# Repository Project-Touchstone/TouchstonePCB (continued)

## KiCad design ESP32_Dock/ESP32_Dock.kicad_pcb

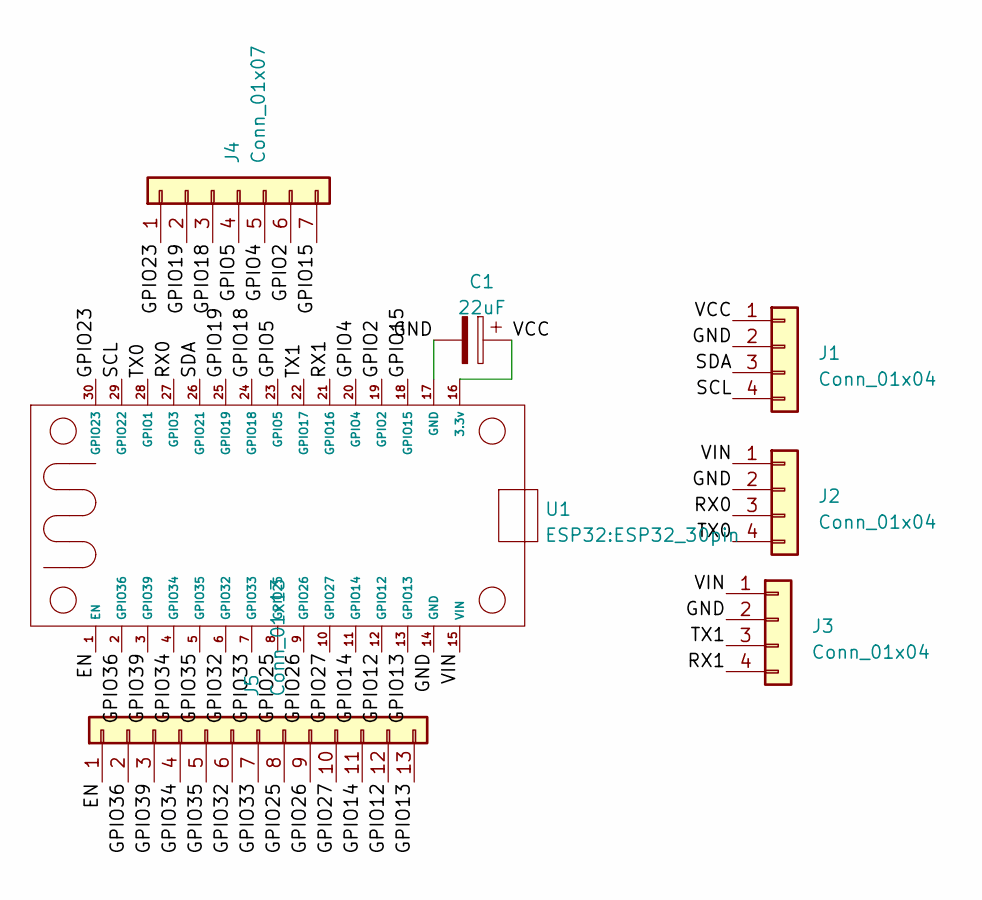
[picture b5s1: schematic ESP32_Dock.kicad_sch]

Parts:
C1: 22uF; C_Radial_D5.0mm_H11.0mm_P2.00mm
J1: Conn_01x04; PinHeader_1x04_P2.54mm_Vertical
J2: Conn_01x04; PinSocket_1x04_P2.54mm_Horizontal
J3: Conn_01x04; PinHeader_1x04_P2.54mm_Horizontal
J4: Conn_01x07; PinHeader_1x07_P2.54mm_Vertical
J5: Conn_01x13; PinHeader_1x13_P2.54mm_Vertical
U1: ESP32_30pin

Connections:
/EN: J5.1, U1.1 (EN)
/GND: C1.2, J1.2, J2.2, J3.2, U1.14 (GND), U1.17 (GND)
/GPIO2: J4.6, U1.19 (GPIO2)
/GPIO4: J4.5, U1.20 (GPIO4)
/GPIO5: J4.4, U1.23 (GPIO5)
/GPIO12: J5.12, U1.12 (GPIO12)
/GPIO13: J5.13, U1.13 (GPIO13)
/GPIO14: J5.11, U1.11 (GPIO14)
/GPIO15: J4.7, U1.18 (GPIO15)
/GPIO18: J4.3, U1.24 (GPIO18)
/GPIO19: J4.2, U1.25 (GPIO19)
/GPIO23: J4.1, U1.30 (GPIO23)
/GPIO25: J5.8, U1.8 (GPIO25)
/GPIO26: J5.9, U1.9 (GPIO26)
/GPIO27: J5.10, U1.10 (GPIO27)
/GPIO32: J5.6, U1.6 (GPIO32)
/GPIO33: J5.7, U1.7 (GPIO33)
/GPIO34: J5.4, U1.4 (GPIO34)
/GPIO35: J5.5, U1.5 (GPIO35)
/GPIO36: J5.2, U1.2 (GPIO36)
/GPIO39: J5.3, U1.3 (GPIO39)
/RX0: J2.3, U1.27 (GPIO3)
/RX1: J3.4, U1.21 (GPIO16)
/SCL: J1.4, U1.29 (GPIO22)
/SDA: J1.3, U1.26 (GPIO21)
/TX0: J2.4, U1.28 (GPIO1)
/TX1: J3.3, U1.22 (GPIO17)
/VCC: C1.1, J1.1, U1.16 (3.3v)
/VIN: J2.1, J3.1, U1.15 (VIN)

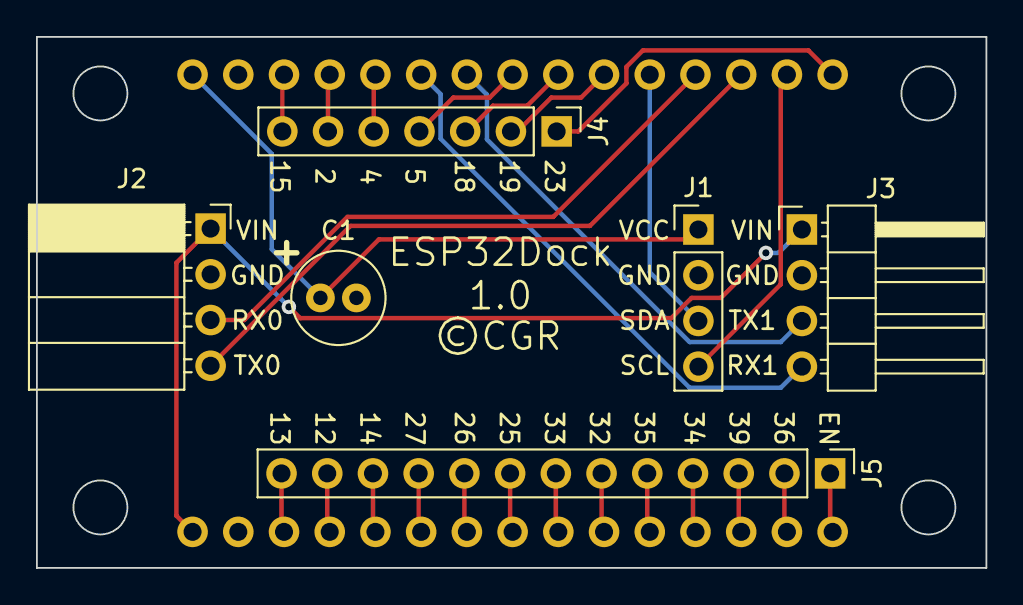
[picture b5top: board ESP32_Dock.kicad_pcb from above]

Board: 2 copper layers, 52.8 x 29.5 mm, 7 parts (1 on the bottom side), 29 nets.

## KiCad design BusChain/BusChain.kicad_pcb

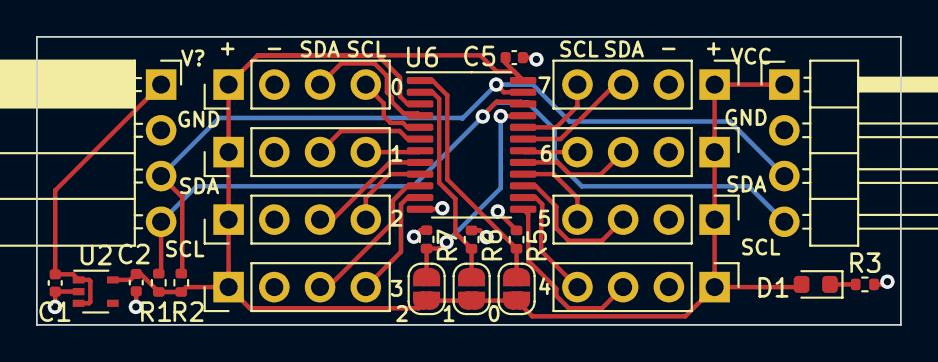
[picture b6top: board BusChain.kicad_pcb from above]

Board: 2 copper layers, 48.0 x 16.0 mm, 25 parts (0 on the bottom side), 25 nets.

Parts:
C1, C2, C5: 0.1u; C_0402_1005Metric
D1: LED; LED_0603_1608Metric
J1: Conn_01x04; PinSocket_1x04_P2.54mm_Horizontal
J2, J3, J4, J5, J6, J7, J8, J9: Conn_01x04; PinHeader_1x04_P2.54mm_Vertical
J10: Conn_01x04; PinHeader_1x04_P2.54mm_Horizontal
JP1, JP2, JP3: Jumper_2_Open; SolderJumper-2_P1.3mm_Open_RoundedPad1.0x1.5mm
R1, R2: 1.2K; R_0402_1005Metric
R3: 500; R_0402_1005Metric
R5, R6, R7: 10K; R_0402_1005Metric
U2: MIC5365-3.3YC5; SOT-353_SC-70-5
U6: TCA9548BPWR; TSSOP-24_4.4x7.8mm_P0.65mm

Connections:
/SC0: J2.4, U6.5 (SC0)
/SC1: J3.4, U6.7 (SC1)
/SC2: J4.4, U6.9 (SC2)
/SC3: J5.4, U6.11 (SC3)
/SC4: J6.4, U6.14 (SC4)
/SC5: J7.4, U6.16 (SC5)
/SC6: J8.4, U6.18 (SC6)
/SC7: J9.4, U6.20 (SC7)
/SCL: J1.4, J10.4, R1.2, U6.22 (SCL)
/SD0: J2.3, U6.4 (SD0)
/SD1: J3.3, U6.6 (SD1)
/SD2: J4.3, U6.8 (SD2)
/SD3: J5.3, U6.10 (SD3)
/SD4: J6.3, U6.13 (SD4)
/SD5: J7.3, U6.15 (SD5)
/SD6: J8.3, U6.17 (SD6)
/SD7: J9.3, U6.19 (SD7)
/SDA: J1.3, J10.3, R2.2, U6.23 (SDA)
/V?: C1.1, J1.1, U2.1 (VIN), U2.3 (EN)
/VCC: C2.1, C5.2, D1.2 (A), J2.1, J3.1, J4.1, J5.1, J6.1, J7.1, J8.1, J9.1, J10.1, JP1.1 (A), JP2.1 (A), JP3.1 (A), R1.1, R2.1, U2.5 (VOUT), U6.3 (~RESET), U6.24 (VCC)
GND: C1.2, C2.2, C5.1, J1.2, J2.2, J3.2, J4.2, J5.2, J6.2, J7.2, J8.2, J9.2, J10.2, R3.2, R5.1, R6.1, R7.1, U2.2 (GND), U6.12 (GND)
unnamed: D1.1 (K), R3.1
unnamed: JP1.2 (B), R7.2, U6.21 (A2)
unnamed: JP2.2 (B), R6.2, U6.2 (A1)
unnamed: JP3.2 (B), R5.2, U6.1 (A0)

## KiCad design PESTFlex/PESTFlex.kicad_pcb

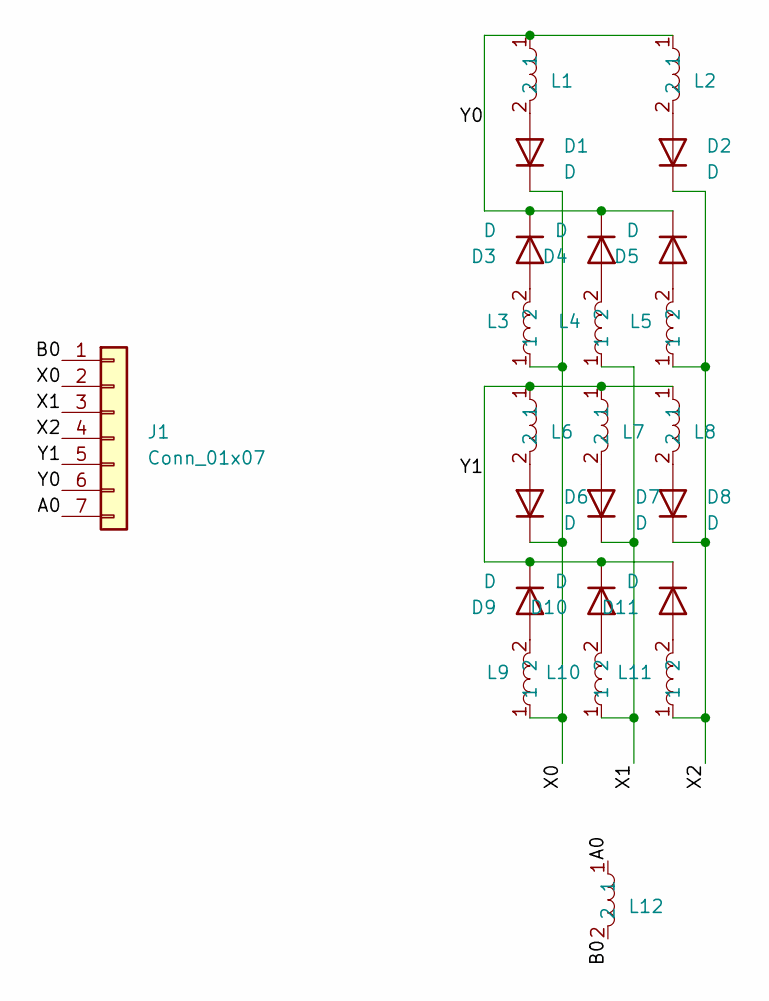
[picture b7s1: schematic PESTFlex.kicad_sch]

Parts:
D1, D2, D3, D4, D5, D6, D7, D8, D9, D10, D11: D; ES2A-L Diode
J1: Conn_01x07; Flex2Driver
L1, L2, L3, L4, L5, L6, L7, L8, L9, L10, L11, L12: PEST_SMD

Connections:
/A0: J1.7, L12.1
/B0: J1.1, L12.2
/X0: D1.1 (K), D6.1 (K), J1.2, L3.1, L9.1
/X1: D7.1 (K), J1.3, L4.1, L10.1
/X2: D2.1 (K), D8.1 (K), J1.4, L5.1, L11.1
/Y0: D3.1 (K), D4.1 (K), D5.1 (K), J1.6, L1.1, L2.1
/Y1: D9.1 (K), D10.1 (K), D11.1 (K), J1.5, L6.1, L7.1, L8.1
unnamed: D1.2 (A), L1.2
unnamed: D2.2 (A), L2.2
unnamed: D3.2 (A), L3.2
unnamed: D4.2 (A), L4.2
unnamed: D5.2 (A), L5.2
unnamed: D6.2 (A), L6.2
unnamed: D7.2 (A), L7.2
unnamed: D8.2 (A), L8.2
unnamed: D9.2 (A), L9.2
unnamed: D10.2 (A), L10.2
unnamed: D11.2 (A), L11.2

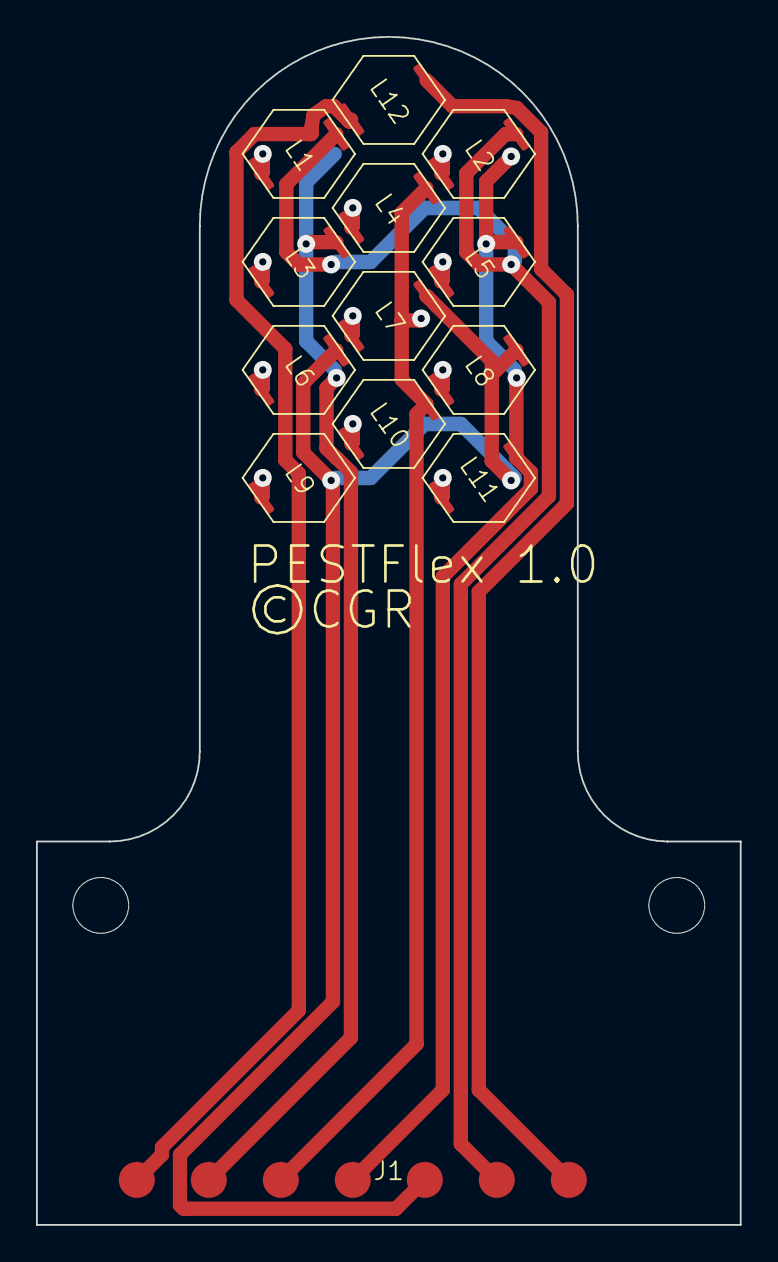
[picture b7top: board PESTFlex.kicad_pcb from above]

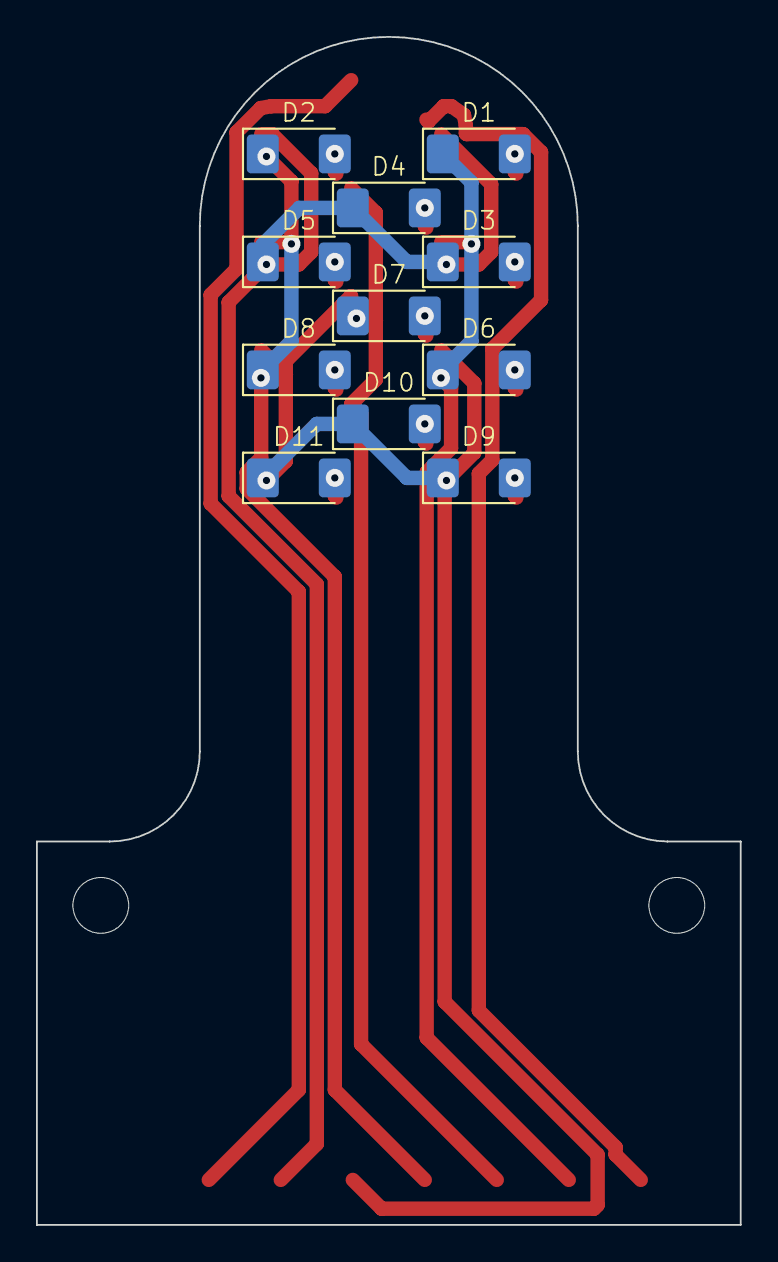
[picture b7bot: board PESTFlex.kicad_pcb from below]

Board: 2 copper layers, 39.1 x 66.0 mm, 24 parts (11 on the bottom side), 18 nets.

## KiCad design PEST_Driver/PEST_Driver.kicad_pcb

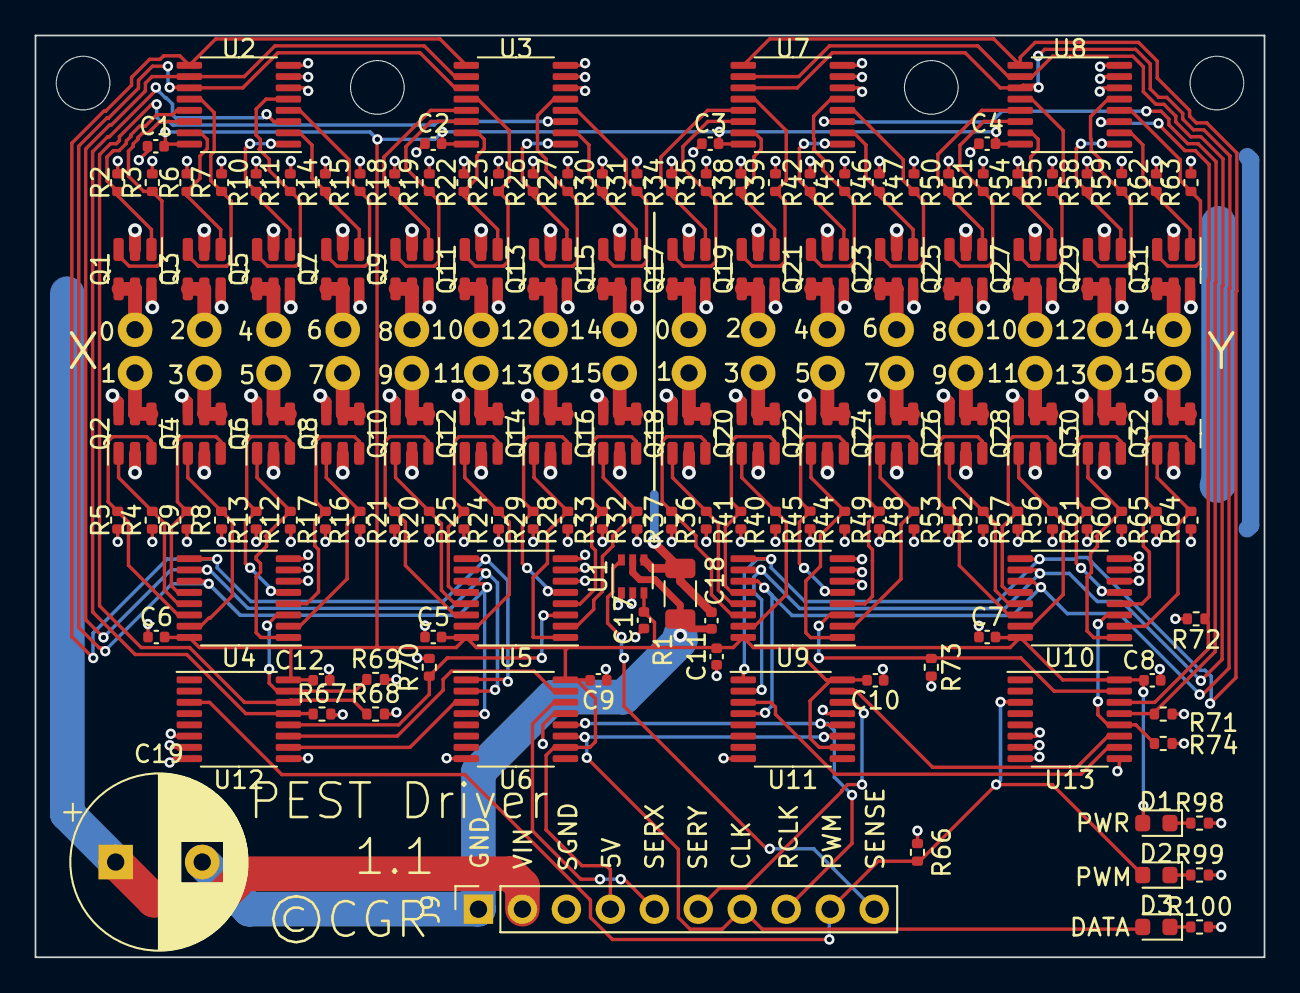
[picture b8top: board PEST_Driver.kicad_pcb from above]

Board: 2 copper layers, 71.0 x 53.2 mm, 157 parts (0 on the bottom side), 128 nets.

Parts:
C1, C2, C3, C4, C5, C6, C7, C8, C9, C10, C11, C12, C17, C18: 0.1u; C_0402_1005Metric
C19: 100u; CP_Radial_D10.0mm_P5.00mm
D1, D2, D3: LED; LED_0603_1608Metric
J1, J2, J3, J4, J5, J6, J7, J8, J10, J11, J12, J13, J14, J15, J16, J17: Conn_01x02; High_Current_Jumper
J9: Conn_01x10; PinSocket_1x10_P2.54mm_Vertical
Q1, Q2, Q3, Q4, Q5, Q6, Q7, Q8, Q9, Q10, Q11, Q12, Q13, Q14, Q15, Q16, Q17, Q18, Q19, Q20, Q21, Q22, Q23, Q24, Q25, Q26, Q27, Q28, Q29, Q30, Q31, Q32: TSOT-23-6
R1: 25m; R_1206_3216Metric
R2, R3, R4, R5, R6, R7, R8, R9, R10, R11, R12, R13, R14, R15, R16, R17, R18, R19, R20, R21, R22, R23, R24, R25, R26, R27, R28, R29, R30, R31, R32, R33, R34, R35, R36, R37, R38, R39, R40, R41, R42, R43, R44, R45, R46, R47, R48, R49, R50, R51, R52, R53, R54, R55, R56, R57, R58, R59, R60, R61, R62, R63, R64, R65, R66, R67, R68, R69, R70, R71, R72, R73, R74: 10K; R_0402_1005Metric
R98, R99, R100: 1.2K; R_0402_1005Metric
U1: INA199xxDCK; SOT-363_SC-70-6
U2, U3, U4, U5, U7, U8, U9, U10, U12, U13: 74HC4051; TSSOP-16_4.4x5mm_P0.65mm
U6, U11: 74HC595; TSSOP-16_4.4x5mm_P0.65mm

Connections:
/X_Control/DIR: U2.11 (S0), U3.11 (S0), U4.11 (S0), U5.11 (S0), U6.4 (QE)
/X_Control/G0A: Q1.1 (G), R2.2, U2.13 (A0)
/X_Control/G0B: Q1.3 (G), R3.1, U2.14 (A1)
/X_Control/G1A: Q2.1 (G), R4.2, U4.13 (A0)
/X_Control/G1B: Q2.3 (G), R5.1, U4.14 (A1)
/X_Control/G2A: Q3.1 (G), R6.2, U2.15 (A2)
/X_Control/G2B: Q3.3 (G), R7.1, U2.12 (A3)
/X_Control/G3A: Q4.1 (G), R8.2, U4.15 (A2)
/X_Control/G3B: Q4.3 (G), R9.1, U4.12 (A3)
/X_Control/G4A: Q5.1 (G), R10.2, U2.1 (A4)
/X_Control/G4B: Q5.3 (G), R11.1, U2.5 (A5)
/X_Control/G5A: Q6.1 (G), R12.2, U4.1 (A4)
/X_Control/G5B: Q6.3 (G), R13.1, U4.5 (A5)
/X_Control/G6A: Q7.1 (G), R14.2, U2.2 (A6)
/X_Control/G6B: Q7.3 (G), R15.1, U2.4 (A7)
/X_Control/G7A: Q8.1 (G), R16.2, U4.2 (A6)
/X_Control/G7B: Q8.3 (G), R17.1, U4.4 (A7)
/X_Control/G8A: Q9.1 (G), R18.2, U3.13 (A0)
/X_Control/G8B: Q9.3 (G), R19.1, U3.14 (A1)
/X_Control/G9A: Q10.1 (G), R20.2, U5.13 (A0)
/X_Control/G9B: Q10.3 (G), R21.1, U5.14 (A1)
/X_Control/G10A: Q11.1 (G), R22.2, U3.15 (A2)
/X_Control/G10B: Q11.3 (G), R23.1, U3.12 (A3)
/X_Control/G11A: Q12.1 (G), R24.2, U5.15 (A2)
/X_Control/G11B: Q12.3 (G), R25.1, U5.12 (A3)
/X_Control/G12A: Q13.1 (G), R26.2, U3.1 (A4)
/X_Control/G12B: Q13.3 (G), R27.1, U3.5 (A5)
/X_Control/G13A: Q14.1 (G), R28.2, U5.1 (A4)
/X_Control/G13B: Q14.3 (G), R29.1, U5.5 (A5)
/X_Control/G14A: Q15.1 (G), R30.2, U3.2 (A6)
/X_Control/G14B: Q15.3 (G), R31.1, U3.4 (A7)
/X_Control/G15A: Q16.1 (G), R32.2, U5.2 (A6)
/X_Control/G15B: Q16.3 (G), R33.1, U5.4 (A7)
/X_Control/OUT0: J1.1, Q1.4 (D), Q1.5 (S)
/X_Control/OUT1: J1.2, Q2.4 (D), Q2.5 (S)
/X_Control/OUT2: J2.1, Q3.4 (D), Q3.5 (S)
/X_Control/OUT3: J2.2, Q4.4 (D), Q4.5 (S)
/X_Control/OUT4: J3.1, Q5.4 (D), Q5.5 (S)
/X_Control/OUT5: J3.2, Q6.4 (D), Q6.5 (S)
/X_Control/OUT6: J4.1, Q7.4 (D), Q7.5 (S)
/X_Control/OUT7: J4.2, Q8.4 (D), Q8.5 (S)
/X_Control/OUT8: J5.1, Q9.4 (D), Q9.5 (S)
/X_Control/OUT9: J5.2, Q10.4 (D), Q10.5 (S)
/X_Control/OUT10: J6.1, Q11.4 (D), Q11.5 (S)
/X_Control/OUT11: J6.2, Q12.4 (D), Q12.5 (S)
/X_Control/OUT12: J7.1, Q13.4 (D), Q13.5 (S)
/X_Control/OUT13: J7.2, Q14.4 (D), Q14.5 (S)
/X_Control/OUT14: J8.1, Q15.4 (D), Q15.5 (S)
/X_Control/OUT15: J8.2, Q16.4 (D), Q16.5 (S)
/X_Control/S0: U6.3 (QD), U12.10 (S1)
/X_Control/S1: U2.10 (S1), U3.10 (S1), U4.10 (S1), U5.10 (S1), U6.2 (QC)
/X_Control/S2: U2.9 (S2), U3.9 (S2), U4.9 (S2), U5.9 (S2), U6.1 (QB)
/X_Control/S3: U6.15 (QA), U12.11 (S0)
/Y_Control/DIR: U7.11 (S0), U8.11 (S0), U9.11 (S0), U10.11 (S0), U11.4 (QE)
/Y_Control/G0A: Q17.1 (G), R34.2, U7.13 (A0)
/Y_Control/G0B: Q17.3 (G), R35.1, U7.14 (A1)
/Y_Control/G1A: Q18.1 (G), R36.2, U9.13 (A0)
/Y_Control/G1B: Q18.3 (G), R37.1, U9.14 (A1)
/Y_Control/G2A: Q19.1 (G), R38.2, U7.15 (A2)
/Y_Control/G2B: Q19.3 (G), R39.1, U7.12 (A3)
/Y_Control/G3A: Q20.1 (G), R40.2, U9.15 (A2)
/Y_Control/G3B: Q20.3 (G), R41.1, U9.12 (A3)
/Y_Control/G4A: Q21.1 (G), R42.2, U7.1 (A4)
/Y_Control/G4B: Q21.3 (G), R43.1, U7.5 (A5)
/Y_Control/G5A: Q22.1 (G), R44.2, U9.1 (A4)
/Y_Control/G5B: Q22.3 (G), R45.1, U9.5 (A5)
/Y_Control/G6A: Q23.1 (G), R46.2, U7.2 (A6)
/Y_Control/G6B: Q23.3 (G), R47.1, U7.4 (A7)
/Y_Control/G7A: Q24.1 (G), R48.2, U9.2 (A6)
/Y_Control/G7B: Q24.3 (G), R49.1, U9.4 (A7)
/Y_Control/G8A: Q25.1 (G), R50.2, U8.13 (A0)
/Y_Control/G8B: Q25.3 (G), R51.1, U8.14 (A1)
/Y_Control/G9A: Q26.1 (G), R52.2, U10.13 (A0)
/Y_Control/G9B: Q26.3 (G), R53.1, U10.14 (A1)
/Y_Control/G10A: Q27.1 (G), R54.2, U8.15 (A2)
/Y_Control/G10B: Q27.3 (G), R55.1, U8.12 (A3)
/Y_Control/G11A: Q28.1 (G), R56.2, U10.15 (A2)
/Y_Control/G11B: Q28.3 (G), R57.1, U10.12 (A3)
/Y_Control/G12A: Q29.1 (G), R58.2, U8.1 (A4)
/Y_Control/G12B: Q29.3 (G), R59.1, U8.5 (A5)
/Y_Control/G13A: Q30.1 (G), R60.2, U10.1 (A4)
/Y_Control/G13B: Q30.3 (G), R61.1, U10.5 (A5)
/Y_Control/G14A: Q31.1 (G), R62.2, U8.2 (A6)
/Y_Control/G14B: Q31.3 (G), R63.1, U8.4 (A7)
/Y_Control/G15A: Q32.1 (G), R64.2, U10.2 (A6)
/Y_Control/G15B: Q32.3 (G), R65.1, U10.4 (A7)
/Y_Control/OUT0: J10.1, Q17.4 (D), Q17.5 (S)
/Y_Control/OUT1: J10.2, Q18.4 (D), Q18.5 (S)
/Y_Control/OUT2: J11.1, Q19.4 (D), Q19.5 (S)
/Y_Control/OUT3: J11.2, Q20.4 (D), Q20.5 (S)
/Y_Control/OUT4: J12.1, Q21.4 (D), Q21.5 (S)
/Y_Control/OUT5: J12.2, Q22.4 (D), Q22.5 (S)
/Y_Control/OUT6: J13.1, Q23.4 (D), Q23.5 (S)
/Y_Control/OUT7: J13.2, Q24.4 (D), Q24.5 (S)
/Y_Control/OUT8: J14.1, Q25.4 (D), Q25.5 (S)
/Y_Control/OUT9: J14.2, Q26.4 (D), Q26.5 (S)
/Y_Control/OUT10: J15.1, Q27.4 (D), Q27.5 (S)
/Y_Control/OUT11: J15.2, Q28.4 (D), Q28.5 (S)
/Y_Control/OUT12: J16.1, Q29.4 (D), Q29.5 (S)
/Y_Control/OUT13: J16.2, Q30.4 (D), Q30.5 (S)
/Y_Control/OUT14: J17.1, Q31.4 (D), Q31.5 (S)
/Y_Control/OUT15: J17.2, Q32.4 (D), Q32.5 (S)
/Y_Control/S0: U11.3 (QD), U13.10 (S1)
/Y_Control/S1: U7.10 (S1), U8.10 (S1), U9.10 (S1), U10.10 (S1), U11.2 (QC)
/Y_Control/S2: U7.9 (S2), U8.9 (S2), U9.9 (S2), U10.9 (S2), U11.1 (QB)
/Y_Control/S3: U11.15 (QA), U13.11 (S0)
CLK: D3.2 (A), J9.7, U6.11 (SRCLK), U11.11 (SRCLK)
GND: C18.1, C19.2, J9.1, R1.2, U1.5 (-)
GNDS: C1.1, C2.1, C3.1, C4.1, C5.1, C6.1, C7.1, C8.1, C9.1, C10.1, C11.1, C12.1, C17.1, J9.3, R2.1, R3.2, R4.1, R5.2, R6.1, R7.2, R8.1, R9.2, R10.1, R11.2, R12.1, R13.2, R14.1, R15.2, R16.1, R17.2, R18.1, R19.2, R20.1, R21.2, R22.1, R23.2, R24.1, R25.2, R26.1, R27.2, R28.1, R29.2, R30.1, R31.2, R32.1, R33.2, R34.1, R35.2, R36.1, R37.2, R38.1, R39.2, R40.1, R41.2, R42.1, R43.2, R44.1, R45.2, R46.1, R47.2, R48.1, R49.2, R50.1, R51.2, R52.1, R53.2, R54.1, R55.2, R56.1, R57.2, R58.1, R59.2, R60.1, R61.2, R62.1, R63.2, R64.1, R65.2, R66.2, R67.2, R68.2, R69.2, R70.2, R71.2, R72.2, R73.2, R74.2, R98.2, R99.2, R100.2, U1.1 (REF), U1.2 (GND), U2.6 (~E), U2.7 (VEE), U2.8 (GND), U3.6 (~E), U3.7 (VEE), U3.8 (GND), U4.6 (~E), U4.7 (VEE), U4.8 (GND), U5.6 (~E), U5.7 (VEE), U5.8 (GND), U6.8 (GND), U6.13 (~OE), U7.6 (~E), U7.7 (VEE), U7.8 (GND), U8.6 (~E), U8.7 (VEE), U8.8 (GND), U9.6 (~E), U9.7 (VEE), U9.8 (GND), U10.6 (~E), U10.7 (VEE), U10.8 (GND), U11.8 (GND), U11.13 (~OE), U12.6 (~E), U12.7 (VEE), U12.8 (GND), U12.9 (S2), U13.6 (~E), U13.7 (VEE), U13.8 (GND), U13.9 (S2)
unnamed: D1.1 (K), R98.1
unnamed: D2.1 (K), R99.1
unnamed: D3.1 (K), R100.1
unnamed: R74.1, U10.3 (A), U13.12 (A3)
unnamed: R67.1, U2.3 (A), U12.13 (A0)
unnamed: R68.1, U3.3 (A), U12.14 (A1)
unnamed: R69.1, U4.3 (A), U12.15 (A2)
unnamed: R70.1, U5.3 (A), U12.12 (A3)
unnamed: R71.1, U7.3 (A), U13.13 (A0)
unnamed: R72.1, U8.3 (A), U13.14 (A1)
unnamed: R73.1, U9.3 (A), U13.15 (A2)
PWM: D2.2 (A), J9.9, R66.1, U12.3 (A), U13.3 (A)
RCLK: J9.8, U6.12 (RCLK), U11.12 (RCLK)
SENSE: C18.2, Q1.2 (S), Q2.2 (S), Q3.2 (S), Q4.2 (S), Q5.2 (S), Q6.2 (S), Q7.2 (S), Q8.2 (S), Q9.2 (S), Q10.2 (S), Q11.2 (S), Q12.2 (S), Q13.2 (S), Q14.2 (S), Q15.2 (S), Q16.2 (S), Q17.2 (S), Q18.2 (S), Q19.2 (S), Q20.2 (S), Q21.2 (S), Q22.2 (S), Q23.2 (S), Q24.2 (S), Q25.2 (S), Q26.2 (S), Q27.2 (S), Q28.2 (S), Q29.2 (S), Q30.2 (S), Q31.2 (S), Q32.2 (S), R1.1, U1.4 (+)
SERX: J9.5, U6.14 (SER)
SERY: J9.6, U11.14 (SER)
VCC: C1.2, C2.2, C3.2, C4.2, C5.2, C6.2, C7.2, C8.2, C9.2, C10.2, C11.2, C12.2, C17.2, D1.2 (A), J9.4, U1.3 (V+), U2.16 (VCC), U3.16 (VCC), U4.16 (VCC), U5.16 (VCC), U6.10 (~SRCLR), U6.16 (VCC), U7.16 (VCC), U8.16 (VCC), U9.16 (VCC), U10.16 (VCC), U11.10 (~SRCLR), U11.16 (VCC), U12.16 (VCC), U13.16 (VCC)
VIN: C19.1, J9.2, Q1.6 (D), Q2.6 (D), Q3.6 (D), Q4.6 (D), Q5.6 (D), Q6.6 (D), Q7.6 (D), Q8.6 (D), Q9.6 (D), Q10.6 (D), Q11.6 (D), Q12.6 (D), Q13.6 (D), Q14.6 (D), Q15.6 (D), Q16.6 (D), Q17.6 (D), Q18.6 (D), Q19.6 (D), Q20.6 (D), Q21.6 (D), Q22.6 (D), Q23.6 (D), Q24.6 (D), Q25.6 (D), Q26.6 (D), Q27.6 (D), Q28.6 (D), Q29.6 (D), Q30.6 (D), Q31.6 (D), Q32.6 (D)
VOUT: J9.10, U1.6

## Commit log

2024-09-06 Finished PEST tile
2024-09-07 Added PEST Driver Board
2024-09-07 Added independent signal ground to schematic
2024-09-08 Updated PEST for SMD mounting
2024-09-12 Finished wiring independent MOSFET and logic grounds
2024-09-12 Widened all power traces for more current support
2024-09-17 Moved all pads to bottom layer
2024-09-27 Added custom hall sensor symbol
2024-09-27 Branch issue fix
2024-09-30 Fixed some PEST tile glitches
2024-10-06 Finalized compact magnetic encoder design
2024-10-06 Added more pulldown resistors to PEST Driver
2024-10-06 Created basic DRIFT bus schematic and fixed PEST driver numbering
2024-10-06 Fixed some silkscreen stuff, started DRIFT bus layout
2024-10-07 Finished BusChain PCB
2024-10-10 Reduced PEST tile to two pins, added SMD footprint
2024-10-10 Finished PESTFlex schematic, added PEST tile symbol
2024-10-12 Finalized PCBs for fabrication
2024-10-12 Finished PEST tile panelization
2024-10-12 Panelized TrackRing
2024-10-12 Created combined stencil
2024-10-26 Resolved various production and testing issues
2024-11-14 Added MPU6050 mockup
2024-12-25 Added reverse header version of TrackRing PCB for finger cap
2025-01-22 Added accelerometer to thimble TrackRing
2025-01-22 Created fabrication files for TrackRingA
2025-01-22 Finished BusChain1.1 and added power daisy-chaining option
2025-01-22 Renamed TrackRing
2025-01-23 Added ESP32 Dock
2025-01-23 Fixed capacitor size on ESP32 dock
2025-01-24 Final fabrication checks
2025-01-27 Finalized CAD files and configurations
2025-02-03 Fixed direction of TrackNode pin header
2025-02-15 Added interactive HTML boms
2025-06-11 Started new encoder board
2025-06-14 Fixed pin header orientation and added silkscreen
2025-06-15 No longer designing custom as5600 board
2025-06-19 Started BLDC driver design
2025-06-23 Finished majority of component implementations
2025-06-24 Finished schematic first draft
2025-06-24 Changed annotations and fixed capacitor ratings
2025-06-24 Fixed some 3d models
2025-06-25 Added second terminal block
2025-06-27 Some progress on motor driver unit layout
2025-07-03 Finished general layout of hydra board
2025-07-15 Component placement mostly finalized
2025-07-18 Finished layout for main hydra board
2025-07-19 Added silkscreen
2025-07-19 Finished hydra shield version
2025-07-19 FIxed typo
2025-08-01 Added textboxes to schematic sections
2025-08-06 Fixed unit conversion
2025-08-07 Started making some changes based on design review
2025-08-07 Improved gitignore
2025-08-09 Mostly finished applying changes from design review
2025-08-10 Finished Hydra modifications
2025-08-10 Finished updating shield board with changes
2025-08-11 Updated git ignore
2025-08-11 Generated fabrication files
2025-08-11 Consolidated pullup resistors to 10k
2025-08-12 Added AS5600 Mockup
2025-08-12 Mispelling
2025-08-12 Changed shield passthrough to pin header
2025-08-13 Updated gitignore
